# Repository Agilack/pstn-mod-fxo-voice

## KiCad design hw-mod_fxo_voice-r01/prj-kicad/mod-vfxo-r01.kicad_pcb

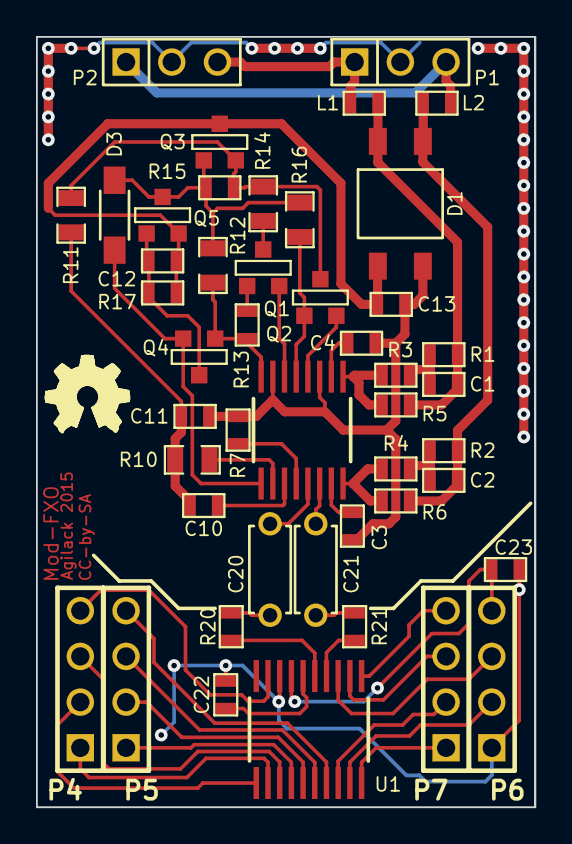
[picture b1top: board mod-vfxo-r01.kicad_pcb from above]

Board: 2 copper layers, 27.7 x 42.8 mm, 47 parts (0 on the bottom side), 50 nets.

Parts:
C1, C2: 120pF; SMD0603
C3, C4, C22: 100nF; SMD0603
C10: 1uF; SMD0603
C11: 2.7nF; SMD0603
C12: 10nF; SMD0603
C13: 3.9nF; SMD0603
C20, C21: 33pF; C_CK05
C23: C; SMD0603
D1: HD04; D-HD04
D3: MMSZ43; SOD-123
L1, L2: FB600; SMD0603
P1, P2: CONN_3
P4, P5, P6, P7: CONN_4
Q1, Q2: MMBTA06; SOT23-3
Q3, Q4: MMBTA42; SOT23-3
Q5: MMBTA92; SOT23-3
R1, R2: 15M; SMD0603
R3, R4: 5.1M; SMD0603
R5, R6: 20M; SMD0603
R7: 1M; SMD0603
R10: 1.07k; SMD0805
R11: 536; SMD0805
R12: 3.65k; SMD0805
R13: 150; SMD0603
R14: 73.2; SMD0805
R15, R17: 100k; SMD0603
R16: 2.49k; SMD0805
R20, R21: 56.2; SMD0603
U1: SI3050-XT; TSSOP20
U2: SI3018; TSSOP16
ohw_logo: VAL**; ohw-logo

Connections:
+3.3V: C23.1, P6.4, U1.17
+Vline: C12.2, C13.1, D1.3, Q3.3, Q5.2, R17.1
GND: C22.2, C23.2, P6.1, U1.18
GNDPWR: C3.2, C4.2, C11.2, C13.2, D1.4, R7.2, U2.11, U2.15
INT: P6.2, U1.9
unnamed: R20.1, U1.15
unnamed: C21.2, U2.6
unnamed: C20.2, U2.5
unnamed: C21.1, R21.2
unnamed: C20.1, R20.2
unnamed: R21.1, U1.14
unnamed: C22.1, U1.16
unnamed: Q2.1, R16.1, U2.13
unnamed: Q2.2, U2.12
unnamed: C12.1, Q4.3, Q5.1, R17.2
unnamed: C4.1, U2.10
unnamed: R7.1, U2.4
unnamed: R4.1, R6.1, U2.8
unnamed: Q1.3, R14.2
unnamed: Q1.2, U2.14
unnamed: Q1.1, R13.2
unnamed: R10.2, U2.2
unnamed: R3.1, R5.1, U2.9
unnamed: C3.1, U2.7
unnamed: L2.2, P1.3, P2.1
unnamed: C1.1, R1.1, R3.2
unnamed: L1.2, P1.1, P2.3
unnamed: C2.1, R2.1, R4.2
unnamed: C1.2, D1.2, L1.1, R1.2, R5.2
unnamed: C2.2, D1.1, L2.1, R2.2, R6.2
unnamed: D3.1, Q4.2, U2.1
unnamed: C10.2, U2.3
unnamed: Q4.1, R12.2, R13.1, U2.16
unnamed: D3.2, Q3.1, Q5.3, R12.1, R15.2, R16.2
unnamed: Q2.3, Q3.2, R11.2, R14.1, R15.1
unnamed: C10.1, C11.1, R10.1, R11.1
PCM_CLK: P5.2, U1.5
PCM_FS: P5.1, U1.4
PCM_RX: P5.4, U1.7
PCM_TX: P5.3, U1.6
RG: P7.1, U1.10
RGDT: P7.2, U1.8
RST: P6.3, U1.13
S_CLK: P4.4, U1.19
S_CS: P4.3, U1.3
S_MISO: P4.2, U1.1
S_MOSI: P4.1, U1.2
Shield: P1.2, P2.2
TGD: P7.4, U1.11
TGDE: P7.3, U1.12

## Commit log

2015-10-07 ADD: module schematics
2015-10-08 = ADD: PCB board design
2015-10-09 =ADD: Production files

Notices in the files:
hw-mod_fxo_voice-r01/prj-kicad/mod-vfxo-r01.kicad_pcb:
CC-by-SA
